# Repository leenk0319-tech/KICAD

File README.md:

# KICAD

## Overview
This project is a 5V ↔ 3.3V bidirectional I2C level shifter PCB based on the PCA9306 (Texas Instruments).  
It enables safe communication between 5V MCUs (e.g., Arduino) and 3.3V sensors.

---

## Key Features
- Bidirectional I2C level shifting using PCA9306
- Supports 5V ↔ 3.3V voltage translation
- Pull-up resistors for SDA and SCL lines
- Decoupling (0.1µF) and bulk capacitors (10µF)
- 2-layer PCB with bottom GND plane
- Gerber and BOM files included

---

## Tools Used
- KiCad 9
- PCA9306 (TI)

---

## Repository Structure

---

## Schematic Preview
(Add schematic image here)

---

## PCB Preview
(Add PCB top / 3D image here)

---

## Manufacturing
Gerber and Drill files are included and ready for fabrication.

---

## Applications
- Arduino ↔ 3.3V sensor interface
- MCU ↔ OLED / IMU / I2C peripherals

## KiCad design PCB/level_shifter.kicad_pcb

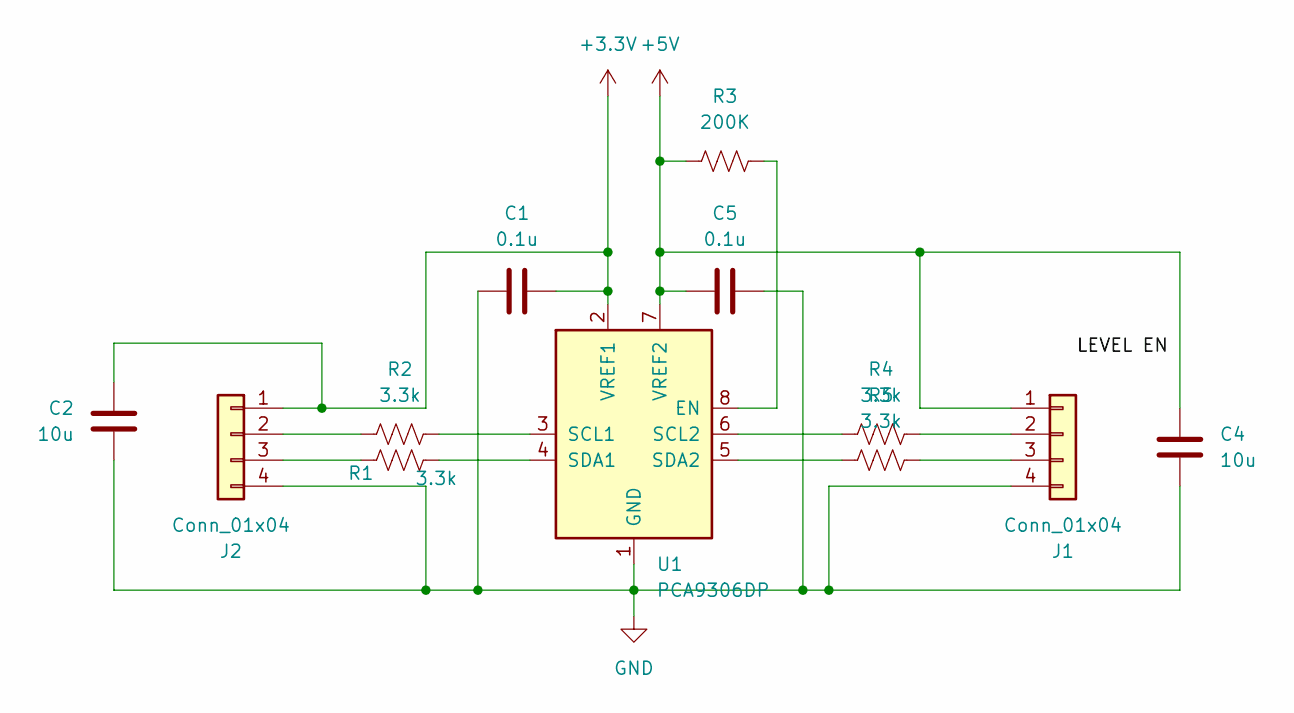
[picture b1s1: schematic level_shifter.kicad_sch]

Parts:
C1, C5: 0.1u; C_0603_1608Metric
C2, C4: 10u; C_0603_1608Metric
J1, J2: Conn_01x04; PinHeader_1x04_P2.54mm_Vertical
R1, R2, R4, R5: 3.3k; R_0603_1608Metric
R3: 200K; R_0603_1608Metric
U1: PCA9306DP; TSSOP-8_3x3mm_P0.65mm

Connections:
+3.3V: C1.2, C2.2, J2.1, U1.2 (VREF1)
+5V: C4.1, C5.1, J1.1, R3.1, U1.7 (VREF2)
GND: C1.1, C2.1, C4.2, C5.2, J1.4, J2.4, U1.1 (GND)
unnamed: J1.2, R4.1
unnamed: J1.3, R5.1
unnamed: J2.2, R2.2
unnamed: J2.3, R1.2
unnamed: R3.2, U1.8 (EN)
unnamed: R2.1, U1.3 (SCL1)
unnamed: R4.2, U1.6 (SCL2)
unnamed: R1.1, U1.4 (SDA1)
unnamed: R5.2, U1.5 (SDA2)

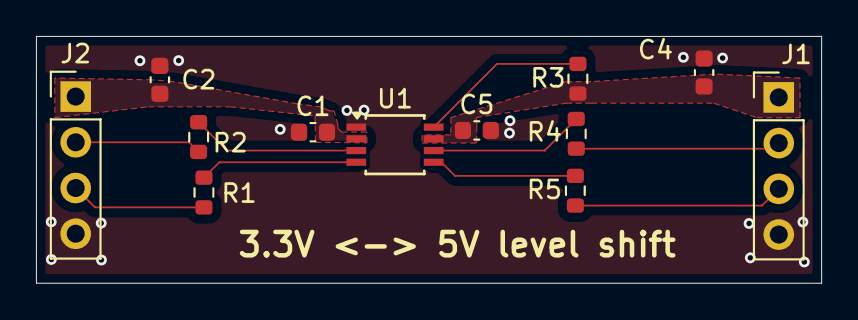
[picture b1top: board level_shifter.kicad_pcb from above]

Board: 2 copper layers, 43.6 x 13.7 mm, 12 parts (0 on the bottom side), 12 nets.

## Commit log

2026-02-08 Expand README with project details and features
    Added project overview, key features, tools used, repository structure, schematic and PCB previews, manufacturing details, applications, and author information.
2026-02-08 Remove author section from README
